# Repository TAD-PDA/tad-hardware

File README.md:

# tad-hardware
Source files for the TAD PDA.

# Kicad files
These are located in tad2-bottom and tad2-top, they are respectively the bottom and top PCB assemblies for the PDA. The folders also include BOMs.

# Case files
The blend file includes the case model, along with key models, to be sliced in your favorite slicing software and 3d printed.

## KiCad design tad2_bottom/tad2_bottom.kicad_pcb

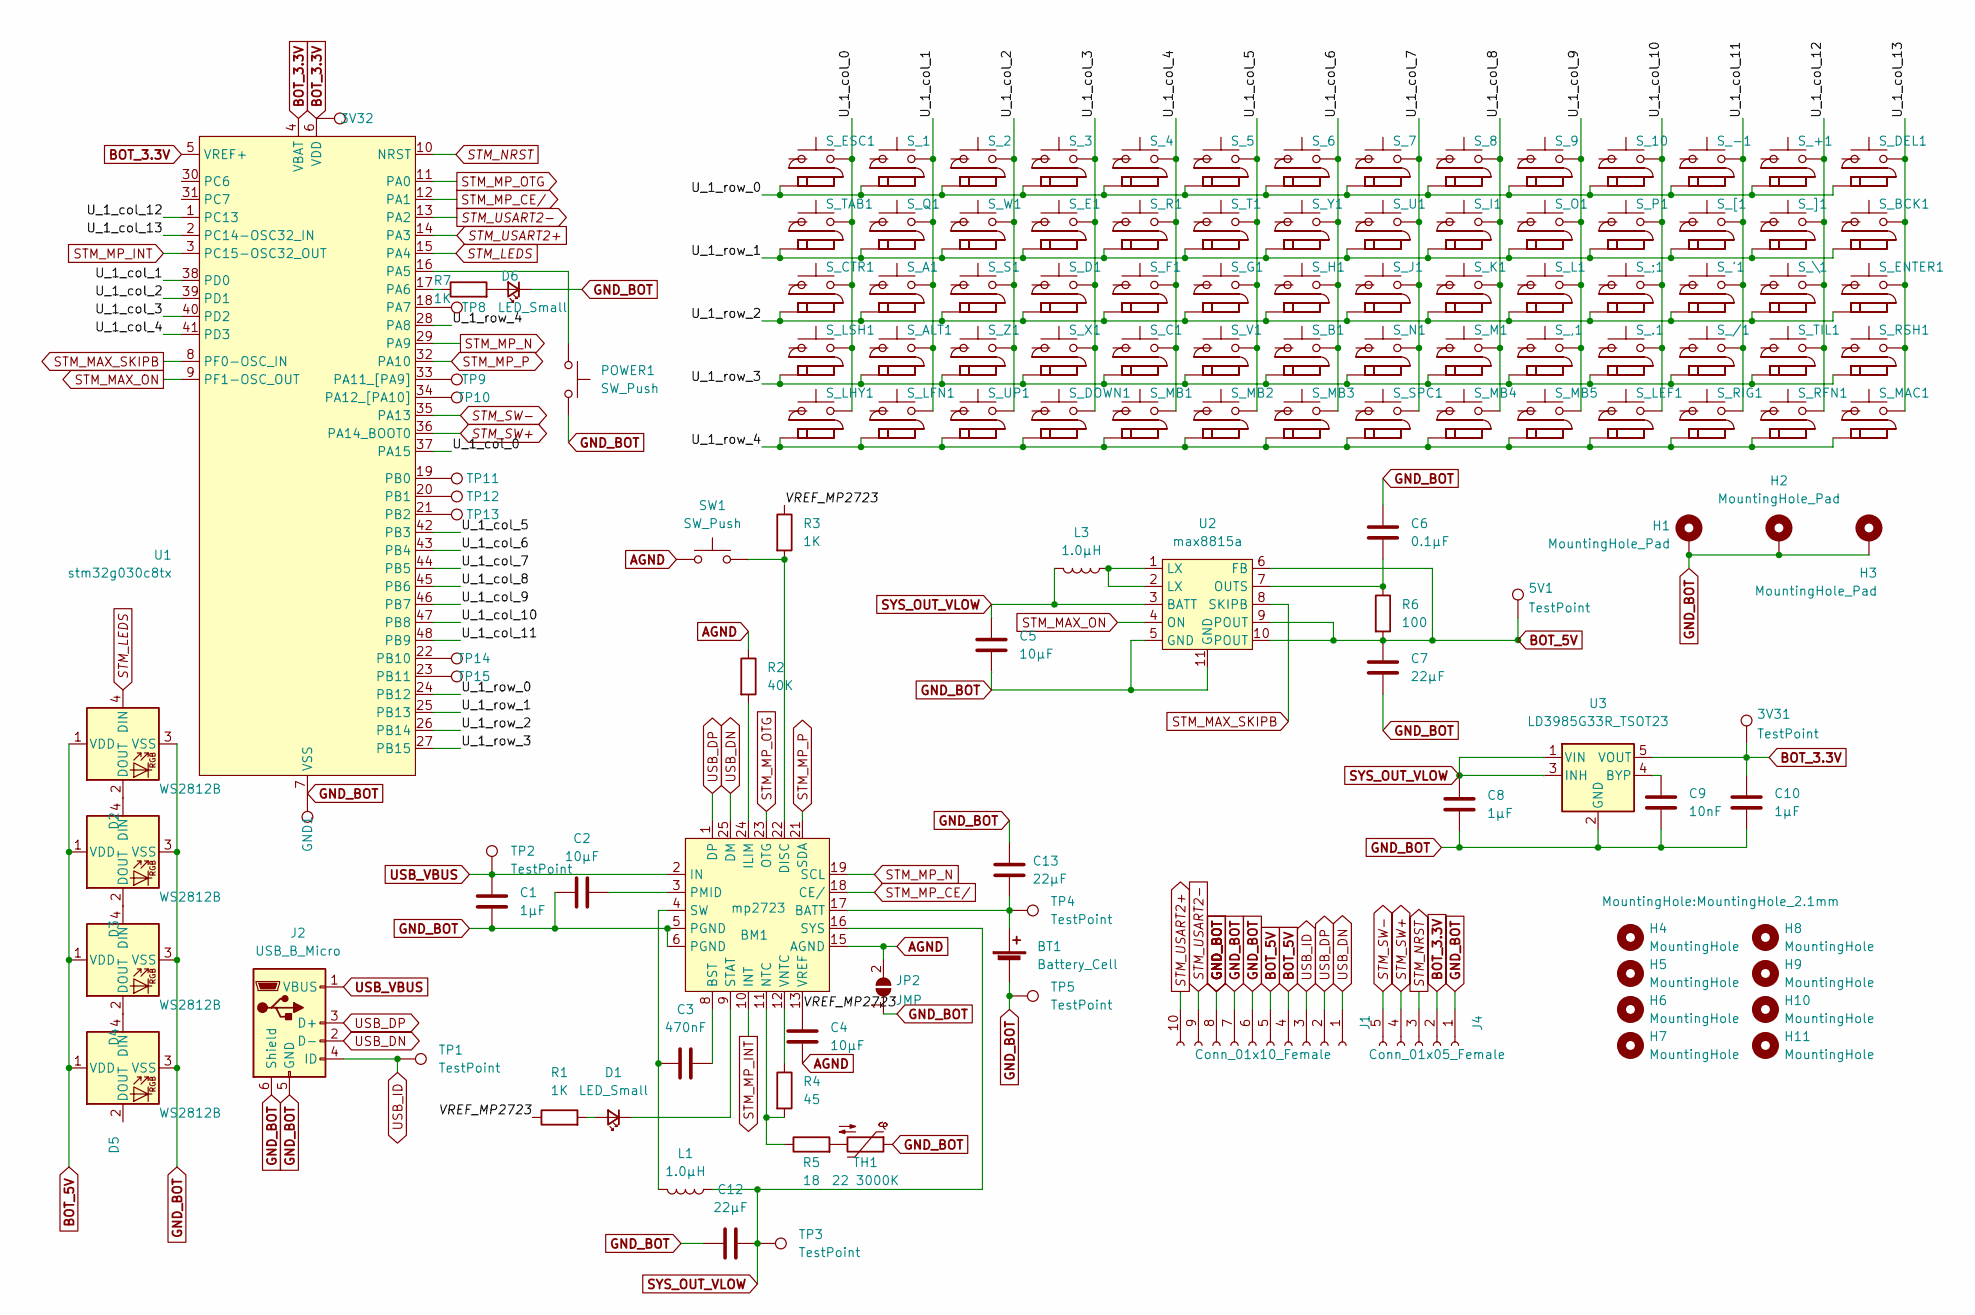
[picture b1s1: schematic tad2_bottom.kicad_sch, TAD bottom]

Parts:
3V31, 3V32, 5V1: TestPoint; TestPoint_Pad_D1.0mm
BM1: mp2723; QFN-26
BT1: Battery_Cell; JST_XH_B2B-XH-AM_1x02_P2.50mm_Vertical
C1, C8, C10: 1μF; C_0805_2012Metric_Pad1.18x1.45mm_HandSolder
C2, C4, C5: 10μF; C_0805_2012Metric_Pad1.18x1.45mm_HandSolder
C3: 470nF; C_0805_2012Metric_Pad1.18x1.45mm_HandSolder
C6: 0.1μF; C_0805_2012Metric_Pad1.18x1.45mm_HandSolder
C7, C12, C13: 22μF; C_0805_2012Metric_Pad1.18x1.45mm_HandSolder
C9: 10nF; C_0805_2012Metric_Pad1.18x1.45mm_HandSolder
D1, D6: LED_Small; LED_D3.0mm
D2, D3, D4, D5: WS2812B; LED_WS2812B_PLCC4_5.0x5.0mm_P3.2mm
GND1: TestPoint; TestPoint_Pad_D1.0mm
H1, H2, H3: MountingHole_Pad; MountingHole_2.5mm_Pad
H4, H5, H6, H7, H8, H9, H10, H11: MountingHole; MountingHole_2.1mm
J1: Conn_01x10_Female; Molex_200528-0100_1x10-1MP_P1.00mm_Horizontal
J2: USB_B_Micro; USB_Micro-B_Molex-105017-0001
J4: Conn_01x05_Female; PinHeader_1x05_P2.54mm_Vertical
JP2: JMP; SolderJumper-2_P1.3mm_Open_RoundedPad1.0x1.5mm
L1, L3: 1.0μH; L_0805_2012Metric_Pad1.05x1.20mm_HandSolder
POWER1: SW_Push; SW_Tactile_SKHH_Angled
R1, R3, R7: 1K; R_0805_2012Metric_Pad1.20x1.40mm_HandSolder
R2: 40K; R_0805_2012Metric_Pad1.20x1.40mm_HandSolder
R4: 45; R_0805_2012Metric_Pad1.20x1.40mm_HandSolder
R5: 18; R_0805_2012Metric_Pad1.20x1.40mm_HandSolder
R6: 100; R_0805_2012Metric_Pad1.20x1.40mm_HandSolder
SW1: SW_Push; SW_SPST_B3U-1000P-B
S_1, S_2, S_3, S_4, S_5, S_6, S_7, S_8, S_9, S_10, S_.1: SW_Push_Diode-tad; SW_PUSH_8mm_silicone_diode
S_'1: SW_Push_Diode-tad; SW_PUSH_8mm_silicone_diode
S_+1: SW_Push_Diode-tad; SW_PUSH_8mm_silicone_diode
S_,1: SW_Push_Diode-tad; SW_PUSH_8mm_silicone_diode
S_-1: SW_Push_Diode-tad; SW_PUSH_8mm_silicone_diode
S_/1: SW_Push_Diode-tad; SW_PUSH_8mm_silicone_diode
S_;1: SW_Push_Diode-tad; SW_PUSH_8mm_silicone_diode
S_A1: SW_Push_Diode-tad; SW_PUSH_8mm_silicone_diode
S_ALT1: SW_Push_Diode-tad; SW_PUSH_8mm_silicone_diode
S_B1: SW_Push_Diode-tad; SW_PUSH_8mm_silicone_diode
S_BCK1: SW_Push_Diode-tad; SW_PUSH_8mm_silicone_diode
S_C1: SW_Push_Diode-tad; SW_PUSH_8mm_silicone_diode
S_CTR1: SW_Push_Diode-tad; SW_PUSH_8mm_silicone_diode
S_D1: SW_Push_Diode-tad; SW_PUSH_8mm_silicone_diode
S_DEL1: SW_Push_Diode-tad; SW_PUSH_8mm_silicone_diode
S_DOWN1: SW_Push_Diode-tad; SW_PUSH_8mm_silicone_diode
S_E1: SW_Push_Diode-tad; SW_PUSH_8mm_silicone_diode
S_ENTER1: SW_Push_Diode-tad; SW_PUSH_8mm_silicone_diode
S_ESC1: SW_Push_Diode-tad; SW_PUSH_8mm_silicone_diode
S_F1: SW_Push_Diode-tad; SW_PUSH_8mm_silicone_diode
S_G1: SW_Push_Diode-tad; SW_PUSH_8mm_silicone_diode
S_H1: SW_Push_Diode-tad; SW_PUSH_8mm_silicone_diode
S_I1: SW_Push_Diode-tad; SW_PUSH_8mm_silicone_diode
S_J1: SW_Push_Diode-tad; SW_PUSH_8mm_silicone_diode
S_K1: SW_Push_Diode-tad; SW_PUSH_8mm_silicone_diode
S_L1: SW_Push_Diode-tad; SW_PUSH_8mm_silicone_diode
S_LEF1: SW_Push_Diode-tad; SW_PUSH_8mm_silicone_diode
S_LFN1: SW_Push_Diode-tad; SW_PUSH_8mm_silicone_diode
S_LHY1: SW_Push_Diode-tad; SW_PUSH_8mm_silicone_diode
S_LSH1: SW_Push_Diode-tad; SW_PUSH_8mm_silicone_diode
S_M1: SW_Push_Diode-tad; SW_PUSH_8mm_silicone_diode
S_MAC1: SW_Push_Diode-tad; SW_PUSH_8mm_silicone_diode
S_MB1, S_MB2, S_MB3, S_MB4, S_MB5: SW_Push_Diode-tad; SW_PUSH_off_board_diode
S_N1: SW_Push_Diode-tad; SW_PUSH_8mm_silicone_diode
S_O1: SW_Push_Diode-tad; SW_PUSH_8mm_silicone_diode
S_P1: SW_Push_Diode-tad; SW_PUSH_8mm_silicone_diode
S_Q1: SW_Push_Diode-tad; SW_PUSH_8mm_silicone_diode
S_R1: SW_Push_Diode-tad; SW_PUSH_8mm_silicone_diode
S_RFN1: SW_Push_Diode-tad; SW_PUSH_8mm_silicone_diode
S_RIG1: SW_Push_Diode-tad; SW_PUSH_8mm_silicone_diode
S_RSH1: SW_Push_Diode-tad; SW_PUSH_8mm_silicone_diode
S_S1: SW_Push_Diode-tad; SW_PUSH_8mm_silicone_diode
S_SPC1: SW_Push_Diode-tad; SW_PUSH_8mm_silicone_diode
S_T1: SW_Push_Diode-tad; SW_PUSH_8mm_silicone_diode
S_TAB1: SW_Push_Diode-tad; SW_PUSH_8mm_silicone_diode
S_TIL1: SW_Push_Diode-tad; SW_PUSH_8mm_silicone_diode
S_U1: SW_Push_Diode-tad; SW_PUSH_8mm_silicone_diode
S_UP1: SW_Push_Diode-tad; SW_PUSH_8mm_silicone_diode
S_V1: SW_Push_Diode-tad; SW_PUSH_8mm_silicone_diode
S_W1: SW_Push_Diode-tad; SW_PUSH_8mm_silicone_diode
S_X1: SW_Push_Diode-tad; SW_PUSH_8mm_silicone_diode
S_Y1: SW_Push_Diode-tad; SW_PUSH_8mm_silicone_diode
S_Z1: SW_Push_Diode-tad; SW_PUSH_8mm_silicone_diode
S_[1: SW_Push_Diode-tad; SW_PUSH_8mm_silicone_diode
S_\1: SW_Push_Diode-tad; SW_PUSH_8mm_silicone_diode
S_]1: SW_Push_Diode-tad; SW_PUSH_8mm_silicone_diode
TH1: 22 3000K; PinHeader_1x02_P2.54mm_Vertical
TP1, TP2, TP3, TP4, TP5, TP8, TP9, TP10, TP11, TP12, TP13, TP14, TP15: TestPoint; TestPoint_Pad_D1.0mm
U1: stm32g030c8tx; LQFP-48_7x7mm_P0.5mm
U2: max8815a; DFN-10-1EP_3x3mm_P0.5mm_EP1.7x2.5mm
U3: LD3985G33R_TSOT23; TSOT-23-5

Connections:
/U_1_col_0: S_CTR1.1 (INPUT), S_ESC1.1 (INPUT), S_LHY1.1 (INPUT), S_LSH1.1 (INPUT), S_TAB1.1 (INPUT), U1.37 (PA15)
/U_1_col_1: S_1.1 (INPUT), S_A1.1 (INPUT), S_ALT1.1 (INPUT), S_LFN1.1 (INPUT), S_Q1.1 (INPUT), U1.38 (PD0)
/U_1_col_2: S_2.1 (INPUT), S_S1.1 (INPUT), S_UP1.1 (INPUT), S_W1.1 (INPUT), S_Z1.1 (INPUT), U1.39 (PD1)
/U_1_col_3: S_3.1 (INPUT), S_D1.1 (INPUT), S_DOWN1.1 (INPUT), S_E1.1 (INPUT), S_X1.1 (INPUT), U1.40 (PD2)
/U_1_col_4: S_4.1 (INPUT), S_C1.1 (INPUT), S_F1.1 (INPUT), S_MB1.1 (INPUT), S_R1.1 (INPUT), U1.41 (PD3)
/U_1_col_5: S_5.1 (INPUT), S_G1.1 (INPUT), S_MB2.1 (INPUT), S_T1.1 (INPUT), S_V1.1 (INPUT), U1.42 (PB3)
/U_1_col_6: S_6.1 (INPUT), S_B1.1 (INPUT), S_H1.1 (INPUT), S_MB3.1 (INPUT), S_Y1.1 (INPUT), U1.43 (PB4)
/U_1_col_7: S_7.1 (INPUT), S_J1.1 (INPUT), S_N1.1 (INPUT), S_SPC1.1 (INPUT), S_U1.1 (INPUT), U1.44 (PB5)
/U_1_col_8: S_8.1 (INPUT), S_I1.1 (INPUT), S_K1.1 (INPUT), S_M1.1 (INPUT), S_MB4.1 (INPUT), U1.45 (PB6)
/U_1_col_9: S_9.1 (INPUT), S_,1.1 (INPUT), S_L1.1 (INPUT), S_MB5.1 (INPUT), S_O1.1 (INPUT), U1.46 (PB7)
/U_1_col_10: S_10.1 (INPUT), S_.1.1 (INPUT), S_;1.1 (INPUT), S_LEF1.1 (INPUT), S_P1.1 (INPUT), U1.47 (PB8)
/U_1_col_11: S_'1.1 (INPUT), S_-1.1 (INPUT), S_/1.1 (INPUT), S_RIG1.1 (INPUT), S_[1.1 (INPUT), U1.48 (PB9)
/U_1_col_12: S_+1.1 (INPUT), S_RFN1.1 (INPUT), S_TIL1.1 (INPUT), S_\1.1 (INPUT), S_]1.1 (INPUT), U1.1 (PC13)
/U_1_col_13: S_BCK1.1 (INPUT), S_DEL1.1 (INPUT), S_ENTER1.1 (INPUT), S_MAC1.1 (INPUT), S_RSH1.1 (INPUT), U1.2 (PC14-OSC32_IN)
/U_1_row_0: S_1.3 (FROM_DIODE), S_2.3 (FROM_DIODE), S_3.3 (FROM_DIODE), S_4.3 (FROM_DIODE), S_5.3 (FROM_DIODE), S_6.3 (FROM_DIODE), S_7.3 (FROM_DIODE), S_8.3 (FROM_DIODE), S_9.3 (FROM_DIODE), S_10.3 (FROM_DIODE), S_+1.3 (FROM_DIODE), S_-1.3 (FROM_DIODE), S_DEL1.3 (FROM_DIODE), S_ESC1.3 (FROM_DIODE), U1.24 (PB12)
/U_1_row_1: S_BCK1.3 (FROM_DIODE), S_E1.3 (FROM_DIODE), S_I1.3 (FROM_DIODE), S_O1.3 (FROM_DIODE), S_P1.3 (FROM_DIODE), S_Q1.3 (FROM_DIODE), S_R1.3 (FROM_DIODE), S_T1.3 (FROM_DIODE), S_TAB1.3 (FROM_DIODE), S_U1.3 (FROM_DIODE), S_W1.3 (FROM_DIODE), S_Y1.3 (FROM_DIODE), S_[1.3 (FROM_DIODE), S_]1.3 (FROM_DIODE), U1.25 (PB13)
/U_1_row_2: S_'1.3 (FROM_DIODE), S_;1.3 (FROM_DIODE), S_A1.3 (FROM_DIODE), S_CTR1.3 (FROM_DIODE), S_D1.3 (FROM_DIODE), S_ENTER1.3 (FROM_DIODE), S_F1.3 (FROM_DIODE), S_G1.3 (FROM_DIODE), S_H1.3 (FROM_DIODE), S_J1.3 (FROM_DIODE), S_K1.3 (FROM_DIODE), S_L1.3 (FROM_DIODE), S_S1.3 (FROM_DIODE), S_\1.3 (FROM_DIODE), U1.26 (PB14)
/U_1_row_3: S_,1.3 (FROM_DIODE), S_.1.3 (FROM_DIODE), S_/1.3 (FROM_DIODE), S_ALT1.3 (FROM_DIODE), S_B1.3 (FROM_DIODE), S_C1.3 (FROM_DIODE), S_LSH1.3 (FROM_DIODE), S_M1.3 (FROM_DIODE), S_N1.3 (FROM_DIODE), S_RSH1.3 (FROM_DIODE), S_TIL1.3 (FROM_DIODE), S_V1.3 (FROM_DIODE), S_X1.3 (FROM_DIODE), S_Z1.3 (FROM_DIODE), U1.27 (PB15)
/U_1_row_4: S_DOWN1.3 (FROM_DIODE), S_LEF1.3 (FROM_DIODE), S_LFN1.3 (FROM_DIODE), S_LHY1.3 (FROM_DIODE), S_MAC1.3 (FROM_DIODE), S_MB1.3 (FROM_DIODE), S_MB2.3 (FROM_DIODE), S_MB3.3 (FROM_DIODE), S_MB4.3 (FROM_DIODE), S_MB5.3 (FROM_DIODE), S_RFN1.3 (FROM_DIODE), S_RIG1.3 (FROM_DIODE), S_SPC1.3 (FROM_DIODE), S_UP1.3 (FROM_DIODE), U1.28 (PA8)
/VREF_MP2723: BM1.13 (VREF), C4.2, R1.1, R3.1
AGND: BM1.15 (AGND), C4.1, JP2.2 (B), R2.1, SW1.1
BOT_3.3V: 3V31.1, 3V32.1, C10.1, J4.2, U1.4 (VBAT), U1.5 (VREF+), U1.6 (VDD), U3.5 (VOUT); also elsewhere on the board
BOT_5V: 5V1.1, C7.1, D2.1 (VDD), D3.1 (VDD), D4.1 (VDD), D5.1 (VDD), J1.4, J1.5, R6.2, U2.6 (FB), U2.9 (POUT), U2.10 (POUT); also elsewhere on the board
GND_BOT: BM1.5 (PGND), BM1.6 (PGND), BT1.2 (-), C1.2, C2.1, C5.1, C6.1, C7.2, C8.2, C9.2, C10.2, C12.1, C13.1, D2.3 (VSS), D3.3 (VSS), D4.3 (VSS), D5.3 (VSS), D6.1 (K), GND1.1, H1.1, H2.1, H3.1, J1.6, J1.7, J1.8, J2.5 (GND), J2.6 (Shield), J4.1, JP2.1 (A), POWER1.2, TH1.1, TP5.1, U1.7 (VSS), U2.5 (GND), U2.11 (GND), U3.2 (GND); also elsewhere on the board
unnamed: BM1.3 (PMID), C2.2
unnamed: BM1.4 (SW), C3.1, L1.2
unnamed: BM1.8 (BST), C3.2
unnamed: BM1.9 (STAT), D1.1 (K)
unnamed: BM1.11 (NTC), R4.2, R5.1
unnamed: BM1.12 (VNTC), R4.1
unnamed: BM1.17 (BATT), BT1.1 (+), C13.2, TP4.1
unnamed: BM1.22 (DISC), R3.2, SW1.2
unnamed: BM1.24 (ILIM), R2.2
unnamed: C6.2, R6.1, U2.7 (OUTS)
unnamed: C9.1, U3.4 (BYP)
unnamed: D1.2 (A), R1.2
unnamed: D2.2 (DOUT), D3.4 (DIN)
unnamed: D2.4 (DIN), U1.15 (PA4)
unnamed: D3.2 (DOUT), D4.4 (DIN)
unnamed: D4.2 (DOUT), D5.4 (DIN)
unnamed: D6.2 (A), R7.2
unnamed: L3.1, U2.1 (LX), U2.2 (LX)
unnamed: POWER1.1, U1.16 (PA5)
unnamed: R5.2, TH1.2
unnamed: TP8.1, U1.18 (PA7)
unnamed: TP9.1, U1.33 (PA11_[PA9])
unnamed: TP10.1, U1.34 (PA12_[PA10])
unnamed: TP11.1, U1.19 (PB0)
unnamed: TP12.1, U1.20 (PB1)
unnamed: TP13.1, U1.21 (PB2)
unnamed: TP14.1, U1.22 (PB10)
unnamed: TP15.1, U1.23 (PB11)
unnamed: R7.1, U1.17 (PA6)
STM_MAX_ON: U1.9 (PF1-OSC_OUT), U2.4 (ON)
STM_MAX_SKIPB: U1.8 (PF0-OSC_IN), U2.8 (SKIPB)
STM_MP_CE/: BM1.18 (CE/), U1.12 (PA1)
STM_MP_INT: BM1.10 (INT), U1.3 (PC15-OSC32_OUT)
STM_MP_N: BM1.19 (SCL), U1.29 (PA9)
STM_MP_OTG: BM1.23 (OTG), U1.11 (PA0)
STM_MP_P: BM1.21 (SDA), U1.32 (PA10)
STM_NRST: J4.3, U1.10 (NRST)
STM_SW+: J4.4, U1.36 (PA14_BOOT0)
STM_SW-: J4.5, U1.35 (PA13)
STM_USART2+: J1.10, U1.14 (PA3)
STM_USART2-: J1.9, U1.13 (PA2)
SYS_OUT_VLOW: BM1.16 (SYS), C5.2, C8.1, C12.2, L1.1, L3.2, TP3.1, U2.3 (BATT), U3.1 (VIN), U3.3 (INH); also elsewhere on the board
USB_DN: BM1.25 (DM), J1.1, J2.2 (D-)
USB_DP: BM1.1 (DP), J1.2, J2.3 (D+)
USB_ID: J1.3, J2.4 (ID), TP1.1
USB_VBUS: BM1.2 (IN), C1.1, J2.1 (VBUS), TP2.1

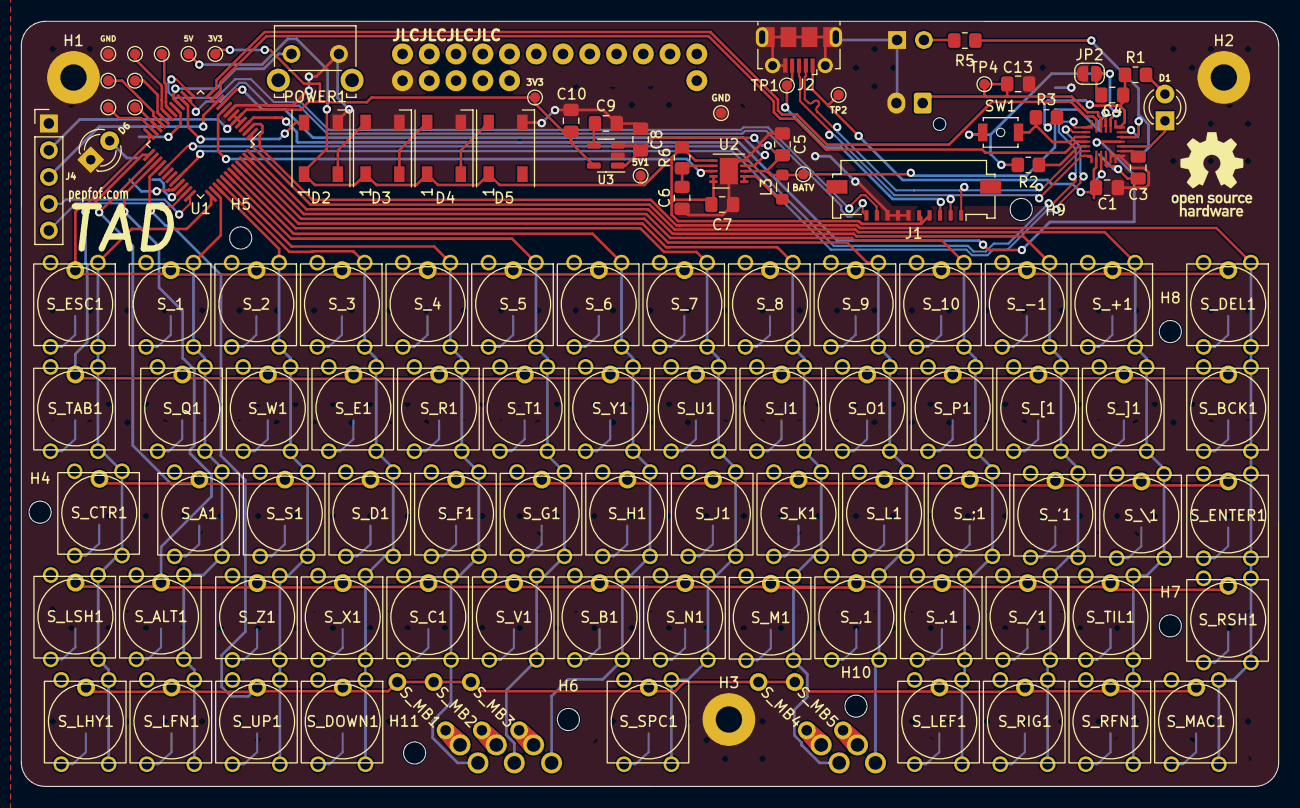
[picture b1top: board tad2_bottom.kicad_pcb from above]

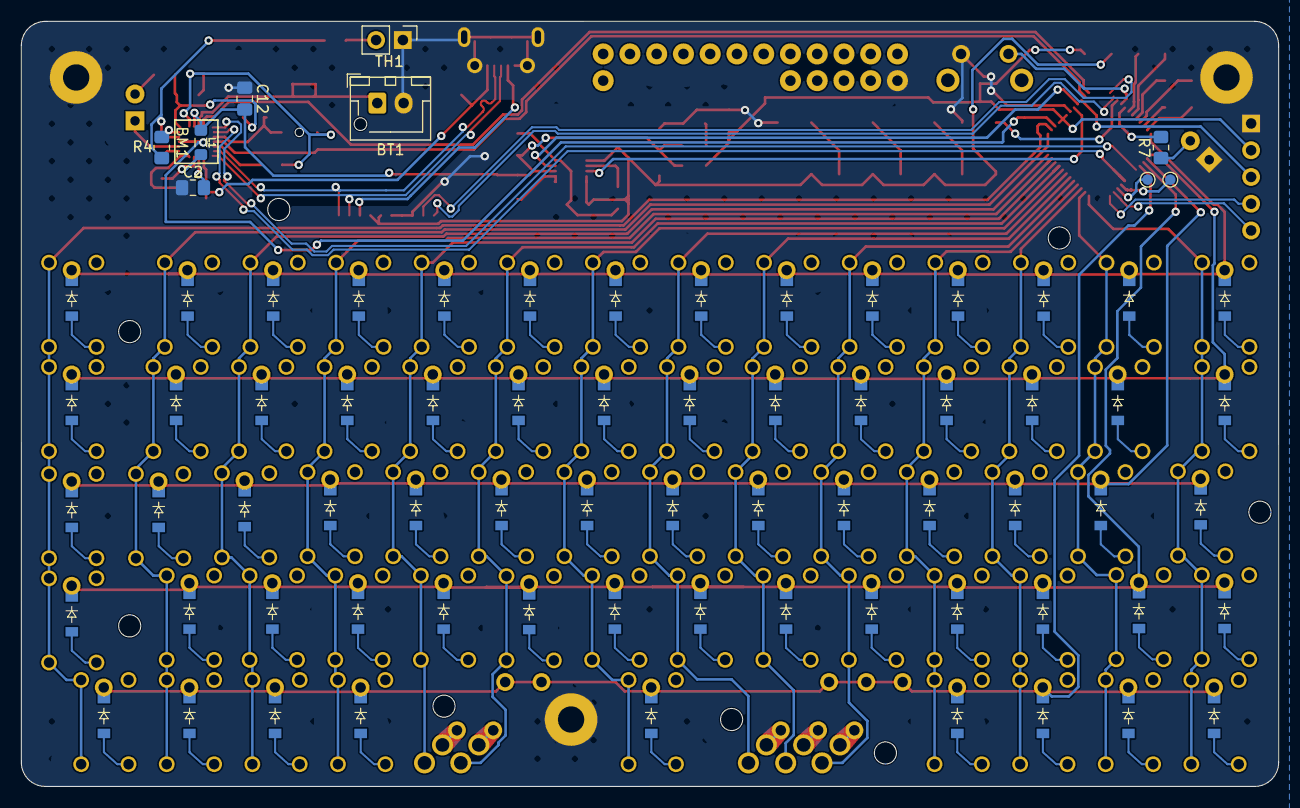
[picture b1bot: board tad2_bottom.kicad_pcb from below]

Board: 2 copper layers, 119.4 x 72.6 mm, 138 parts (9 on the bottom side), 70 nets.

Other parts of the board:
3V3, 3V3#2, 5V: TestPoint; TestPoint_Pad_D1.0mm
BATV: TestPoint; TestPoint_Pad_D1.0mm
GND: TestPoint; TestPoint_Pad_D1.0mm
GND#2: TestPoint; TestPoint_Pad_D1.0mm

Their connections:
BOT_3.3V: 3V3.1, 3V3#2.1; also elsewhere on the board
BOT_5V: 5V.1; also elsewhere on the board
GND_BOT: GND.1, GND#2.1; also elsewhere on the board
SYS_OUT_VLOW: BATV.1; also elsewhere on the board

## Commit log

2023-05-31 Added case model
